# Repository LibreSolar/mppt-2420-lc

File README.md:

# MPPT Charger 20A

 Outdated design, development of new revision ongoing.

**Important:** As we are currently developing a new revision of this charge controller with several improvements, it is not recommended to rebuild this device anymore. Please see [this forum thread](https://talk.libre.solar/t/community-development-of-new-20a-mppt/121) and feel free to contribute your ideas.

## Features:
- 20A MPPT charger (buck converter)
- 55V max PV input
- 12V or 24V battery output
- 32bit ARM MCU (STM32F072)
- CAN communication interface with CANopen standard RJ45 jacks (including 10V power supply)
- Expandable via Olimex Universal Extension Connector (UEXT) featuring I2C, Serial and SPI interface (e.g. used for display, WIFI communication, etc.)
- Compatible to Hammond Mfg 1591XXCFL housing
- 5V switchable signal output
- USB connector for programming etc.
- Can be used as boost converter with software change
- Suitable for Li-Ion batteries with BMS (even recharge after low voltage disconnect possible, as the charge controller increases the voltage automatically when enoug sunlight is available)

## Built-in protection:
- Overvoltage
- Undervoltage
- Overcurrent
- PV short circuit
- PV reverse polarity (for max. module open circuit voltage of around 40V)
- Battery reverse polarity (destructive, fuse is blown)

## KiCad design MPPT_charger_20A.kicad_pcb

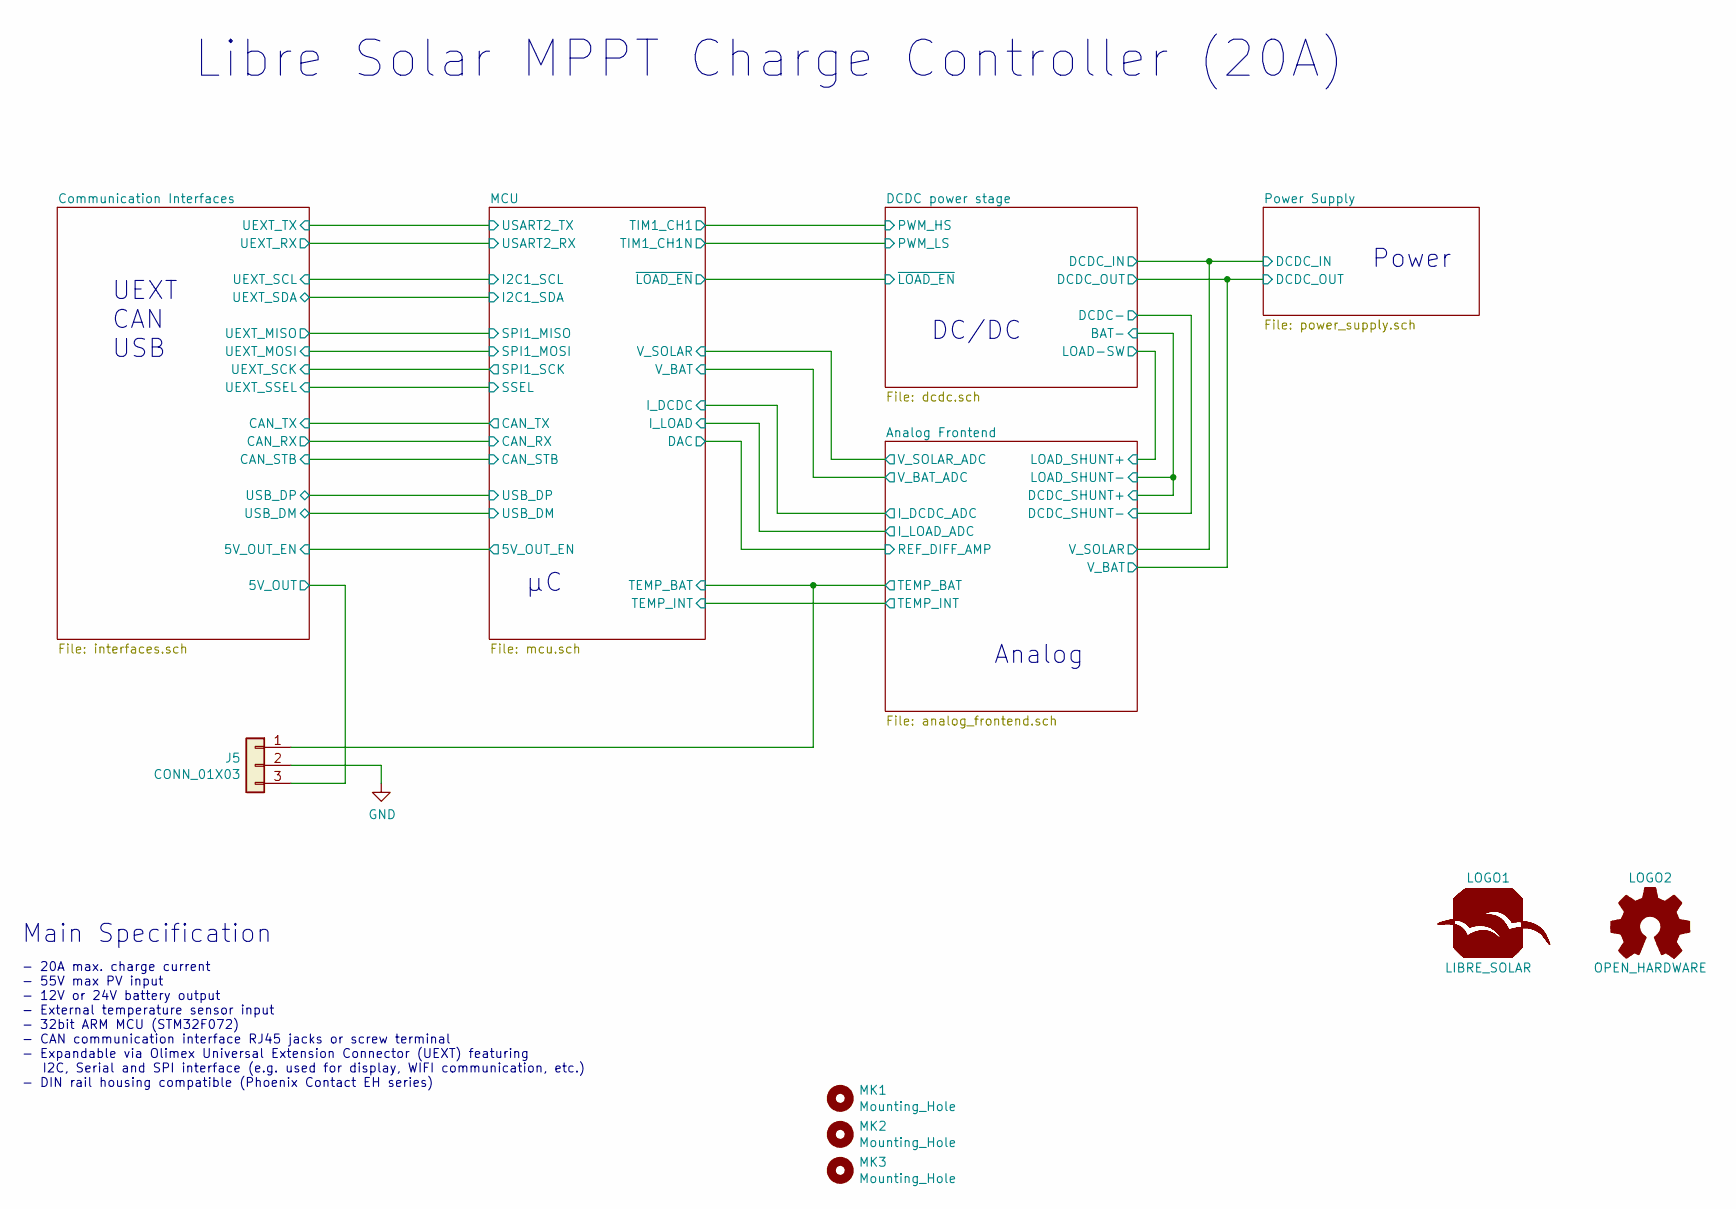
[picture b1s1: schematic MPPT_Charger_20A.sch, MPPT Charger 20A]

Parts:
J5: CONN_01X03; Phoenix_Contact_MC_1,5_3-G-3,81; PartNumber 1803280
LOGO1: LIBRE_SOLAR; LIBRESOLAR_LOGO
LOGO2: OPEN_HARDWARE; OSHW-Logo_5.7x6mm_SilkScreen
MK1, MK2, MK3: Mounting_Hole; MountingHole_3.2mm_M3

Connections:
/Analog Frontend/TEMP_BAT: J5.1; also elsewhere on the board
/Communication Interfaces/5V_OUT: J5.3; also elsewhere on the board
GND: J5.2; also elsewhere on the board

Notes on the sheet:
Libre Solar MPPT Charge Controller (20A)
Main Specification
- 20A max. charge current - 55V max PV input - 12V or 24V battery output - External temperature sensor input - 32bit ARM MCU (STM32F072) - CAN communication interface RJ45 jacks or screw terminal - Expandable via Olimex Universal Extension Connector (UEXT) featuring I2C, Serial and SPI interface (e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
UEXT CAN USB
DC/DC
Analog
Power

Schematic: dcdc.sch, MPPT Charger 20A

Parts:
C1, C2: 1000u; CP_Radial_D16.0mm_P7.50mm; PartNumber EKYB630ELL102ML25S
C3, C4: 4.7u; C_1210_3225; PartNumber GRJ32DC72A475KE11L
C5: 820u; CP_Radial_D10.0mm_P5.00mm; PartNumber EEU-FR1V821L
C6: 1n; C_0603_1608; PartNumber GRM1885C2A102JA01D
C7, C8, C27: 1u; C_0805_2012; PartNumber GRJ21BC72A105KE11L
C10: 100n; C_0603_1608; PartNumber GRM188R71H104KA93D
C12: 2.2u; C_0603_1608; PartNumber GRM188R61E225KA12D
C28: 10n; C_0603_1608; PartNumber GRM188R71H103KA01J
D1: 1N4148; D_SOD-123; PartNumber 1N4148W-7-F
D5: SMBJ36A; D_SMB; PartNumber SMBJ36A
F1: 25A; KEYSTONE-FUSE-3557-2; PartNumber 3557-2
J1: SOLAR; Phoenix_Contact_MKDS_5-2-952; PartNumber 1714971
J2: LOAD; Phoenix_Contact_MKDS_5-2-952; PartNumber 1714971
J3: BAT; Phoenix_Contact_MKDS_5-2-952; PartNumber 1714971
L1: 22uH; L-FERYSTER-DTMSS-27; PartNumber DTMSS-27/0,022/30-H
Q1, Q2, Q3, Q4: CSD18540Q5B; 5X6_MOSFET; PartNumber CSD18540Q5BT
R1, R3, R10: 3.3; R_0805_2012; PartNumber RC0805FR-073R3L
R2: 1M; R_0603_1608; PartNumber RC0603FR-071ML
R4: 2.2; R_1206_3216; PartNumber RC1206FR-072R2L
R6, R17: 2m; R_Bourns_CRE2512; PartNumber CRE2512-FZ-R002E-3
R9: 56k; R_0603_1608; PartNumber RC0603FR-0756KL
R12, R13: 2.2k; R_0603_1608; PartNumber RC0603FR-072K2L
R16: 10k; R_0603_1608; PartNumber RC0603FR-0710KL
T1: MMBT3904; SOT-23; PartNumber MMBT3904-7-F
U1: LM5107; SOIC-8_3.9x4.9mm_Pitch1.27mm; PartNumber LM5107MAX/NOPB

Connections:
+10V: C12.1, R9.2, U1.1 (VDD); also elsewhere on the board
/DCDC power stage/BAT+: C7.1, F1.2, J3.2
/DCDC power stage/BAT-: C7.2, J3.1, R6.2, R17.1; also elsewhere on the board
/DCDC power stage/DCDC_IN: C1.1, C2.1, C3.1, C4.1, C8.1, J1.2, Q1.D; also elsewhere on the board
/DCDC power stage/HS_DRV: R1.2, U1.7 (HO)
/DCDC power stage/LOAD-: C27.2, C28.2, D5.2 (A), J2.2, Q3.D
/DCDC power stage/LOAD-SW: Q3.S, R16.1, R17.2, T1.2 (E); also elsewhere on the board
/DCDC power stage/LS_DRV: R3.2, U1.5 (LO)
/DCDC power stage/PWM_HS: U1.2 (HI); also elsewhere on the board
/DCDC power stage/PWM_LS: U1.3 (LI); also elsewhere on the board
/DCDC power stage/SOLAR-: C8.2, J1.1, Q2.D
/DCDC power stage/SW_NODE: C10.2, L1.1, Q1.S, Q4.D, R4.2, U1.6 (HS)
/DCDC power stage/~LOAD_EN: R13.2; also elsewhere on the board
/DCDC_OUT: C5.1, C27.1, D5.1 (K), F1.1, J2.1, L1.2; also elsewhere on the board
GND: C1.2, C2.2, C3.2, C4.2, C5.2, C6.2, C12.2, Q2.S, Q4.S, R2.1, R6.1, U1.4 (VSS); also elsewhere on the board
unnamed: C6.1, R4.1
unnamed: C10.1, R10.1
unnamed: C28.1, Q3.G, R12.1
unnamed: D1.1, Q2.G, R2.2
unnamed: D1.2, Q4.G, R3.1
unnamed: Q1.G, R1.1
unnamed: R10.2, U1.8 (HB)
unnamed: R9.1, R12.2, T1.3 (C)
unnamed: R13.1, R16.2, T1.1 (B)

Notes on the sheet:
Solar Panel Voltage: 16-55 V
DC/DC power stage
Load output
MOSFET driver
Alternative: 330R at MOSFET gate --> 10.4/330 = 31 mA max
If not stated otherwise, all MLCC 50V X7R
MKDS_5/2-9,52
typisch: 1-10 nF + 10 uF

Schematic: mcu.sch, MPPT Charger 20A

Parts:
C22, C29, C30, C31, C32, C34: 100n; C_0603_1608; PartNumber GRM188R71H104KA93D
C33, C36: 2.2u; C_0603_1608; PartNumber GRM188R61E225KA12D
D6: LM4040CYM3-2.5; SOT-23; PartNumber LM4040DYM3-2.5-TR
L4: 600R; L_0603_1608Metric; PartNumber BLM18AG601SN1D
LED1: LED_red; LED_0603_1608Metric; PartNumber LTST-C190KRKT
LED2: LED_green; LED_0603_1608Metric; PartNumber LTST-C190GKT
P1: CONN_01X02; PinHeader_1x02_P2.54mm_Vertical
R31, R32, R41: 2.2k; R_0603_1608; PartNumber RC0603FR-072K2L
R37: 10k; R_0603_1608; PartNumber RC0603FR-0710KL
R39, R40: 1M; R_0603_1608; PartNumber RC0603FR-071ML
R42, R43: 330; R_0603_1608; PartNumber RC0603FR-07330RL
R45: 56k; R_0603_1608; PartNumber RC0603FR-0756KL
SW1: SW_PUSH; SW_SPST_EVQP7A; PartNumber PTS840 GK SMTR LFS
SWD1: ST_Nucleo_SWD; PinHeader_1x06_P2.54mm_Vertical
T2: MMBT3904; SOT-23; PartNumber MMBT3904-7-F
U2: STM32F072CB; LQFP-48_7x7mm_P0.5mm; PartNumber STM32F072CBT6
U6: 24AA01; SOT-23-5; PartNumber 24AA32AFT-I/OT
Y1: 8MHz; Resonator_Murata_CSTCE_G; PartNumber CSTCE8M00G15C99-R0

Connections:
+3V3: C22.1, C30.1, C31.1, C32.1, C33.1, L4.1, R31.2, R32.2, R37.2, R39.2, R40.2, SWD1.1 (VCC), U2.1 (VBAT), U2.24 (VDD_1), U2.36 (VDD_2), U2.48 (VDD_3), U6.4 (VCC); also elsewhere on the board
/Analog Frontend/TEMP_BAT: U2.10 (PA0-WKUP); also elsewhere on the board
/Analog Frontend/TEMP_INT: U2.11 (PA1); also elsewhere on the board
/Communication Interfaces/5V_OUT_EN: U2.25 (PB12); also elsewhere on the board
/Communication Interfaces/CAN_RX: U2.45 (PB8); also elsewhere on the board
/Communication Interfaces/CAN_STB: U2.38 (PA15); also elsewhere on the board
/Communication Interfaces/CAN_TX: U2.46 (PB9); also elsewhere on the board
/Communication Interfaces/UEXT_EN: U2.3 (PC14-OSC32_IN); also elsewhere on the board
/Communication Interfaces/UEXT_RX: U2.13 (PA3); also elsewhere on the board
/Communication Interfaces/UEXT_TX: U2.12 (PA2); also elsewhere on the board
/Communication Interfaces/USB_DM: U2.32 (PA11); also elsewhere on the board
/Communication Interfaces/USB_DP: U2.33 (PA12); also elsewhere on the board
/Communication Interfaces/V_BUS_EN: U2.4 (PC15-OSC32_OUT); also elsewhere on the board
/DCDC power stage/PWM_HS: U2.29 (PA8); also elsewhere on the board
/DCDC power stage/PWM_LS: U2.26 (PB13); also elsewhere on the board
/DCDC power stage/~LOAD_EN: U2.20 (PB2); also elsewhere on the board
/MCU/BOOT0: C36.1, R39.1, R41.2, U2.44 (BOOT0)
/MCU/DAC: U2.14 (PA4); also elsewhere on the board
/MCU/I2C1_SCL: U2.42 (PB6); also elsewhere on the board
/MCU/I2C1_SDA: U2.43 (PB7); also elsewhere on the board
/MCU/I2C2_SCL: R31.1, U2.21 (PB10), U6.1 (SCL)
/MCU/I2C2_SDA: R32.1, U2.22 (PB11), U6.3 (SDA)
/MCU/I_DCDC: U2.19 (PB1); also elsewhere on the board
/MCU/I_LOAD: U2.18 (PB0); also elsewhere on the board
/MCU/LED1: R42.2, U2.27 (PB14)
/MCU/LED2: R43.2, U2.28 (PB15)
/MCU/OSC_IN: U2.5 (PD0-OSC_IN), Y1.1
/MCU/OSC_OUT: U2.6 (PD1-OSC_OUT), Y1.3
/MCU/SPI1_MISO: U2.40 (PB4); also elsewhere on the board
/MCU/SPI1_MOSI: U2.41 (PB5); also elsewhere on the board
/MCU/SPI1_SCK: U2.39 (PB3); also elsewhere on the board
/MCU/SSEL: U2.2 (PC13-TAMPER-RTC); also elsewhere on the board
/MCU/SWCLK: SWD1.2 (SWCLK), U2.37 (PA14)
/MCU/SWDIO: SWD1.4 (SWDIO), U2.34 (PA13)
/MCU/USART1_RX: P1.2, U2.31 (PA10)
/MCU/USART1_TX: P1.1, U2.30 (PA9)
/MCU/V_BAT: U2.16 (PA6); also elsewhere on the board
/MCU/V_REF: D6.1 (K), R37.1, U2.15 (PA5)
/MCU/V_SOLAR: U2.17 (PA7); also elsewhere on the board
/MCU/~RESET: C29.1, R40.1, R45.1, SW1.1, SWD1.5 (NRST), U2.7 (NRST)
GND: C22.2, C29.2, C30.2, C31.2, C32.2, C33.2, C34.2, C36.2, D6.2 (A), LED1.1, LED2.1, SW1.2, SWD1.3 (GND), T2.2 (E), U2.8 (VSSA), U2.23 (VSS_1), U2.35 (VSS_2), U2.47 (VSS_3), U6.2 (GND), U6.5 (WP), Y1.2; also elsewhere on the board
unnamed: C34.1, L4.2, U2.9 (VDDA)
unnamed: LED1.2, R42.1
unnamed: LED2.2, R43.1
unnamed: R41.1, T2.3 (C)
unnamed: R45.2, T2.1 (B)

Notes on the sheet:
Status LEDs
MCU STM32F072
STM Nucleo SWD and USART
min. 65 uA operating current
Voltage reference
Reset and boot circuit
Tight tolerance for CAN interface
Equations: tau = R39 * C36 = 2.2 s V(t) = Vmax * (1-exp(-t/tau)) --> t = -tau * ln(1-V/Vmax) Normal startup: BOOT0 < 0.69 V Press SW1 < 0.51 s USB bootloader: BOOT0 > 1.61 V Press SW1 > 1.47 s
EEPROM
If not stated otherwise, all MLCC 50V X7R

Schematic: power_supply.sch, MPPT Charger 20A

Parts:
C14: 1u; C_0805_2012; PartNumber GRJ21BC72A105KE11L
C15: 4.7u; C_1210_3225; PartNumber GRJ32DC72A475KE11L
C19: 100n; C_0603_1608; PartNumber GRM188R71H104KA93D
C20, C21, C24: 10u; C_0805_2012; PartNumber GRM21BR61E106KA73L
C23, C38: 2.2u; C_0603_1608; PartNumber GRM188R61E225KA12D
C35: 100p; C_0603_1608; PartNumber GRM1885C2A101JA01D
D2: SS16FP; D_PowerDI-123; PartNumber SS16FP
L2: 4.7uH; L_0805_2012Metric; PartNumber LQM21PN4R7NGRD
L3: 47uH; Bourns_SRN6045TA; PartNumber NR6045T470M
R28: 110k; R_0603_1608; PartNumber RC0603FR-07110KL
R29: 10k; R_0603_1608; PartNumber RC0603FR-0710KL
R50: 1M; R_0603_1608; PartNumber RC0603FR-071ML
U3: AZ1117; SOT-223-3_TabPin2; PartNumber AZ1117EH-5.0TRG1
U4: MP2459; SOT-23-6; PartNumber MP2459GJ-Z
U5: AP2210-3.3; SOT-23-5; PartNumber AP2210K-3.3TRG1

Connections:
+3V3: C38.1, U5.5 (OUT); also elsewhere on the board
+5V: C23.1, C24.1, U3.2 (OUT), U5.1 (IN), U5.3 (EN); also elsewhere on the board
+10V: C20.1, C21.1, L3.2, R28.1, U3.3 (IN); also elsewhere on the board
/DCDC power stage/DCDC_IN: C14.1, L2.1; also elsewhere on the board
GND: C14.2, C15.2, C20.2, C21.2, C23.2, C24.2, C35.2, C38.2, D2.2, R29.2, U3.1 (GND), U4.2 (GND), U5.2 (GND); also elsewhere on the board
unnamed: C15.1, L2.2, R50.2, U4.5 (Vin)
unnamed: C19.1, U4.1 (CB)
unnamed: C19.2, D2.1, L3.1, U4.6 (SW)
unnamed: C35.1, U5.4 (BP)
unnamed: R28.2, R29.1, U4.3 (FB)
unnamed: R50.1, U4.4 (EN)

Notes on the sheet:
Max current output: 150mA
Solar/Battery to 10V (SMPS)
5V to 3.3V (LDO)
Place close to SMPS
10V to 5V (LDO)
Advantages of DCDC_IN as input: - Power supply possible through solar or battery (via HS MOSFET body diode) - Discharged Li-ion batteries (with enabled cut-off switch) can be recharged
If not stated otherwise, all MLCC 50V X7R
MP2459: R50 necessary to limit current into EN to <100uA R28 selection: 110k for MP2459 (9.7 V) 120k for LMR16006X (10 V)

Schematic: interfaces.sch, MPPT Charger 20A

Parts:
C25, C26, C39: 100n; C_0603_1608; PartNumber GRM188R71H104KA93D
D3: USBLC6-2SC6Y; SOT-23-6; PartNumber USBLC6-2SC6Y
D4: NUP2105L; SOT-23; PartNumber NUP2105LT1G
D8: MM3Z12VT1G; D_SOD-323; PartNumber MM3Z12VT1G
D9, D10: 1N4148; D_SOD-123; PartNumber 1N4148W-7-F
F2, F3: 200mA; R_1206_3216; PartNumber 0ZCJ0020FF2E
J4: UEXT; Box_Header_2x05x2.54mm_Straight
JP1, JP2: RJ45_NS; RJ45_8P8C; PartNumber 54602-908LF
JP3: Jumper_NC_Small; PinHeader_1x02_P2.54mm_Horizontal
P3: USB Micro B; USB_Micro-B_10103594-0001LF; PartNumber 10103594-0001LF
Q5, Q6, Q7: BSS84; SOT-23; PartNumber BSS84
R5, R33, R46, R47: 100k; R_0603_1608; PartNumber RC0603FR-07100KL
R30, R49: 56k; R_0603_1608; PartNumber RC0603FR-0756KL
R34, R35, R38: 2.2k; R_0603_1608; PartNumber RC0603FR-072K2L
R36: 120; R_1206_3216; PartNumber RC1206FR-07120RL
R48: 10k; R_0603_1608; PartNumber RC0603FR-0710KL
T3, T4: MMBT3904; SOT-23; PartNumber MMBT3904-7-F
U8: TJA1042T/3; SOIC-8_3.9x4.9mm_Pitch1.27mm; PartNumber TJA1042T/3/1J

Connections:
+3V3: C39.1, Q6.2 (S), R5.1, R34.2, R35.2, U8.5 (VIO); also elsewhere on the board
+5V: C26.1, F2.1, Q5.2 (S), R33.1, U8.3 (VCC); also elsewhere on the board
/Communication Interfaces/5V_OUT: Q5.3 (D); also elsewhere on the board
/Communication Interfaces/5V_OUT_EN: R47.2; also elsewhere on the board
/Communication Interfaces/CAN_GND: D10.2, JP1.3, JP1.7, JP2.3, JP2.7
/Communication Interfaces/CAN_H: D4.1, JP1.1, JP2.1, JP3.1, U8.7 (CANH)
/Communication Interfaces/CAN_L: D4.2, JP1.2, JP2.2, R36.2, U8.6 (CANL)
/Communication Interfaces/CAN_RX: U8.4 (RXD); also elsewhere on the board
/Communication Interfaces/CAN_SHLD: JP1.6, JP2.6
/Communication Interfaces/CAN_STB: U8.8 (STB); also elsewhere on the board
/Communication Interfaces/CAN_TX: U8.1 (TXD); also elsewhere on the board
/Communication Interfaces/CAN_V+: D9.1, JP1.8, JP2.8
/Communication Interfaces/RJ45_4: JP1.4, JP2.4
/Communication Interfaces/RJ45_5: JP1.5, JP2.5
/Communication Interfaces/UEXT_EN: Q6.1 (G), R5.2; also elsewhere on the board
/Communication Interfaces/UEXT_RX: J4.4 (RXD); also elsewhere on the board
/Communication Interfaces/UEXT_TX: J4.3 (TXD); also elsewhere on the board
/Communication Interfaces/USB_DM: D3.3 (IO2); also elsewhere on the board
/Communication Interfaces/USB_DP: D3.1 (IO1); also elsewhere on the board
/Communication Interfaces/V_BUS_EN: R48.2; also elsewhere on the board
/DCDC_OUT: D8.1 (K), Q7.2 (S), R49.1; also elsewhere on the board
/MCU/I2C1_SCL: J4.5 (SCL), R35.1; also elsewhere on the board
/MCU/I2C1_SDA: J4.6 (SDA), R34.1; also elsewhere on the board
/MCU/SPI1_MISO: J4.7 (MISO); also elsewhere on the board
/MCU/SPI1_MOSI: J4.8 (MOSI); also elsewhere on the board
/MCU/SPI1_SCK: J4.9 (SCK); also elsewhere on the board
/MCU/SSEL: J4.10 (SSEL); also elsewhere on the board
GND: C25.2, C26.2, C39.2, D3.2 (GND), D4.3, D10.1, J4.2 (GND), P3.5 (GND), R46.2, T3.2 (E), T4.2 (E), U8.2 (GND); also elsewhere on the board
unnamed: C25.1, P3.6 (Shield)
unnamed: D3.4 (IO2), P3.2 (D-)
unnamed: D3.5 (VBUS), F2.2, P3.1 (VBUS)
unnamed: D3.6 (IO1), P3.3 (D+)
unnamed: D8.2 (A), Q7.1 (G), R30.1, R49.2
unnamed: D9.2, F3.1
unnamed: F3.2, Q7.3 (D)
unnamed: J4.1 (3V3), Q6.3 (D)
unnamed: JP3.2, R36.1
unnamed: P3.4 (ID), R46.1
unnamed: Q5.1 (G), R33.2, R38.1
unnamed: R30.2, T3.3 (C)
unnamed: R38.2, T4.3 (C)
unnamed: R47.1, T4.1 (B)
unnamed: R48.1, T3.1 (B)

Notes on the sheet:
CAN interface
Extension connector
I2C pull-ups
USB connector
5V signal output
ToDo: check R47 --> should be smaller?
Bus power supply
If not stated otherwise, all MLCC 50V X7R

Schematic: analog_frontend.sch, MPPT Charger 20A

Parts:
C9, C16, C40, C42: 100n; C_0603_1608; PartNumber GRM188R71H104KA93D
C11, C13, C17, C18: 10n; C_0603_1608; PartNumber GRM188R71H103KA01J
R7, R8, R11, R18, R19, R20: 2.2k; R_0603_1608; PartNumber RC0603FR-072K2L
R14, R15, R21, R22: 150k; R_0603_1608; PartNumber RC0603FR-07150KL
R23, R27, R44: 10k; R_0603_1608; PartNumber RC0603FR-0710KL
R24, R25: 100k; R_0603_1608; PartNumber RC0603FR-07100KL
R26: 5.6k; R_0603_1608; PartNumber RC0603FR-075K6L
RT1: 10k; R_0603_1608; PartNumber NTCG163JF103FT1S
U7: LM258; SOIC-8_3.9x4.9mm_Pitch1.27mm; PartNumber LM258DR

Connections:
+3V3: R23.1, R44.1; also elsewhere on the board
+5V: C9.1, U7.8 (V+); also elsewhere on the board
/Analog Frontend/TEMP_BAT: C40.1, R44.2; also elsewhere on the board
/Analog Frontend/TEMP_INT: C16.1, R23.2, RT1.1; also elsewhere on the board
/DCDC power stage/BAT-: R7.2, R19.2; also elsewhere on the board
/DCDC power stage/DCDC_IN: R24.1; also elsewhere on the board
/DCDC power stage/LOAD-SW: R8.2; also elsewhere on the board
/DCDC_OUT: R25.1; also elsewhere on the board
/MCU/DAC: C42.1, R14.1, R21.2; also elsewhere on the board
/MCU/I_DCDC: C13.1, R20.2; also elsewhere on the board
/MCU/I_LOAD: C11.1, R11.2; also elsewhere on the board
/MCU/V_BAT: C18.1, R25.2, R27.1; also elsewhere on the board
/MCU/V_SOLAR: C17.1, R24.2, R26.1; also elsewhere on the board
GND: C9.2, C11.2, C13.2, C16.2, C17.2, C18.2, C40.2, C42.2, R18.2, R26.2, R27.2, RT1.2, U7.4 (V-); also elsewhere on the board
unnamed: R11.1, R15.2, U7.7
unnamed: R8.1, R14.2, U7.5 (+)
unnamed: R7.1, R15.1, U7.6 (-)
unnamed: R18.1, R22.1, U7.2 (-)
unnamed: R19.1, R21.1, U7.3 (+)
unnamed: R20.1, R22.2, U7.1

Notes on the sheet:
Load current
DCDC current
Solar and battery voltage
Diff. amp. reference defined by DAC pin instead of GND: variable zero current set point
If not stated otherwise, all MLCC 50V X7R
Temperature (ext./int.)

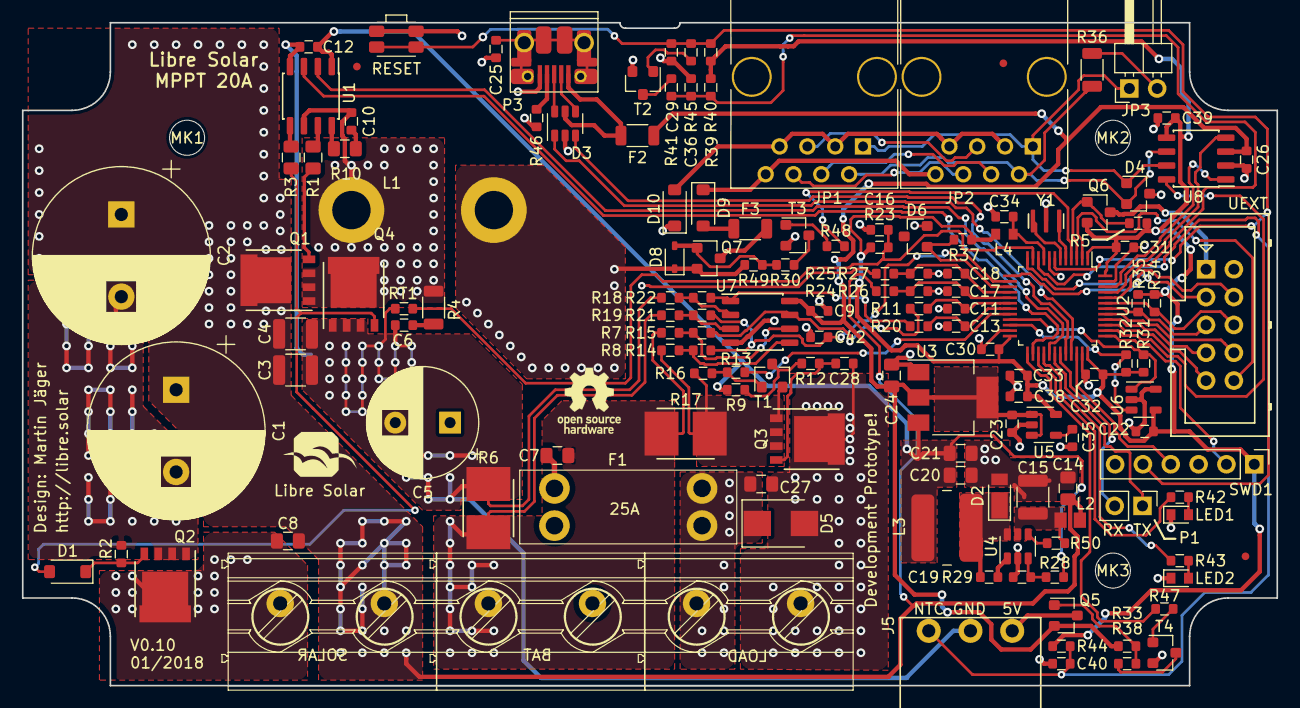
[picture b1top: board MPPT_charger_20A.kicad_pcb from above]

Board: 2 copper layers, 114.5 x 60.5 mm, 146 parts (0 on the bottom side), 102 nets.

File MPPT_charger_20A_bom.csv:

Component;Description;Part;References;Value;Footprint;Quantity Per PCB;Datasheet;Remarks;PartNumber;Manufacturer;Alternative;Supplier
1;Polarised capacitor;CP_Small;C1 C2;1000u;CP_Radial_D16.0mm_P7.50mm;2;;63V, 2.74A, 16x25;EKYB630ELL102ML25S;United Chemi-Con;;
2;Unpolarized capacitor;C_Small;C9 C10 C16 C19 C22 C25 C26 C29 C30 C31 C32 C34 C39 C40 C42;100n;C_0603_1608;15;;;GRM188R71H104KA93D;Murata;;
3;Unpolarized capacitor;C_Small;C35;100p;C_0603_1608;1;;;GRM1885C2A101JA01D;Murata;;
4;Unpolarized capacitor;C_Small;C11 C13 C17 C18 C28;10n;C_0603_1608;5;;;GRM188R71H103KA01J;Murata;;
5;Unpolarized capacitor;C_Small;C20 C21 C24;10u;C_0805_2012;3;;25V;GRM21BR61E106KA73L;Murata;;
6;Unpolarized capacitor;C_Small;C6;1n;C_0603_1608;1;;NP0/C0G;GRM1885C2A102JA01D;Murata;;
7;Unpolarized capacitor;C_Small;C7 C8 C14 C27;1u;C_0805_2012;4;;100V, X7S;GRJ21BC72A105KE11L;Murata;;
8;Unpolarized capacitor;C_Small;C12 C23 C33 C36 C38;2.2u;C_0603_1608;5;;25V, X5R;GRM188R61E225KA12D;Murata;;
9;Unpolarized capacitor;C_Small;C3 C4 C15;4.7u;C_1210_3225;3;;100V, X7S;GRJ32DC72A475KE11L;Murata;;
10;Polarised capacitor;CP_Small;C5;820u;CP_Radial_D10.0mm_P5.00mm;1;;35V, 2.47A;EEU-FR1V821L;Panasonic;;
11;Diode, small symbol;D_Small;D1 D9 D10;1N4148;D_SOD-123;3;;;1N4148W-7-F;Diodes Inc.;;
12;Zener Diode, small symbol;D_Zener_Small;D6;LM4040CYM3-2.5;SOT-23;1;https://en.wikipedia.org/wiki/Zener_diode;;LM4040DYM3-2.5-TR;Microchip;;
13;Zener Diode, small symbol;D_Zener_Small;D8;MM3Z12VT1G;D_SOD-323;1;https://en.wikipedia.org/wiki/Zener_diode;;MM3Z12VT1G;ON Semiconductor;;
14;;NUP2105L;D4;NUP2105L;SOT-23;1;;;NUP2105LT1G;ON Semiconductor;SZNUP2105L;
15;Zener Diode, small symbol;D_Zener_Small;D5;SMBJ36A;D_SMB;1;https://en.wikipedia.org/wiki/Zener_diode;;SMBJ36A;Bourns;;
16;Schottky diode, small symbol;D_Schottky_Small;D2;SS16FP;D_PowerDI-123;1;;;SS16FP;Diodes Inc.;DFLS160-7;
17;;USBLC6-2SC6;D3;USBLC6-2SC6Y;SOT-23-6;1;;;USBLC6-2SC6Y;STMicroelectronics;;
18;resettable fuse, polymeric positive temperature coefficient (PPTC);Polyfuse;F2 F3;200mA;R_1206_3216;2;;;0ZCJ0020FF2E;Bel;;
19;Fuse, small symbol;Fuse_Small;F1;25A;KEYSTONE-FUSE-3557-2;1;;;3557-2;Keystone;;
20;;Screw_Terminal_1x02;J3;BAT;Phoenix_Contact_MKDS_5-2-952;1;;;1714971;Phoenix Contact;;
21;Generic connector, single row, 01x03;Conn_01x03;J5;CONN_01X03;Phoenix_Contact_MC_1,5_3-G-3,81;1;;;1803280;Phoenix Contact;;
22;;Screw_Terminal_1x02;J2;LOAD;Phoenix_Contact_MKDS_5-2-952;1;;;1714971;Phoenix Contact;;
23;;Screw_Terminal_1x02;J1;SOLAR;Phoenix_Contact_MKDS_5-2-952;1;;;1714971;Phoenix Contact;;
24;;UEXT;J4;UEXT;Box_Header_2x05x2.54mm_Straight;1;;;;;;
25;Jumper, normally closed;Jumper_NC_Small;JP3;Jumper_NC_Small;Pin_Header_Angled_1x02_Pitch2.54mm;1;;;;;;
26;;RJ45_NS;JP1 JP2;RJ45_NS;RJ45_8P8C;2;;;54602-908LF;Amphenol FCI;;
27;Inductor with Iron Core;L_Core_Iron;L1;22uH;L-FERYSTER-DTMSS-27;1;;;DTMSS-27/0,022/30-H;Feryster;;Feryster
28;Inductor, small symbol;L_Small;L2;4.7uH;L_0805;1;;;LQM21PN4R7NGRD;Murata;;
29;Inductor, small symbol;L_Small;L3;47uH;Bourns_SRN6045TA;1;;;NR6045T470M;Tayo Yuden;Bourns SRR6045TA-470Y;
30;Inductor, small symbol;L_Small;L4;600R;L_0603;1;;;BLM18AG601SN1D;Murata;;
31;LED, small symbol;LED_Small;LED2;LED_green;LED_0603;1;;;LTST-C190GKT;Lite-On;;
32;LED, small symbol;LED_Small;LED1;LED_red;LED_0603;1;;red;LTST-C190KRKT;Lite-On;;
33;Generic connector, single row, 01x02;Conn_01x02;P1;CONN_01X02;Pin_Header_Straight_1x02_Pitch2.54mm;1;;;;;;
34;USB Micro Type B connector;USB_B_Micro;P3;USB Micro B;USB_Micro-B_10103594-0001LF;1;;;10103594-0001LF;FCI;;Mouser
35;Transistor P-MOSFET with substrate diode (general);Q_PMOS_GSD;Q5 Q6 Q7;BSS84;SOT-23;3;;;BSS84;Fairchild;;
36;Transistor N-MOSFET (general);Q_NMOS;Q1 Q2 Q3 Q4;CSD18540Q5B;5X6_MOSFET;4;;;CSD18540Q5BT;Texas Instruments;;
37;Resistor, small symbol;R_Small;R5 R24 R25 R33 R46 R47;100k;R_0603_1608;6;;;RC0603FR-07100KL;Yageo;;
38;Resistor, small symbol;R_Small;R16 R23 R27 R29 R37 R44 R48;10k;R_0603_1608;7;;;RC0603FR-0710KL;Yageo;;
39;Resistor, small symbol;R_Small;R28;110k;R_0603_1608;1;;;RC0603FR-07110KL;Yageo;;
40;Resistor, small symbol;R_Small;R36;120;R_1206_3216;1;;;RC1206FR-07120RL;Yageo;;
41;Resistor, small symbol;R_Small;R14 R15 R21 R22;150k;R_0603_1608;4;;;RC0603FR-07150KL;Yageo;;
42;Resistor, small symbol;R_Small;R2 R39 R40 R50;1M;R_0603_1608;4;;;RC0603FR-071ML;Yageo;;
43;Resistor, small symbol;R_Small;R4;2.2;R_1206_3216;1;;;RC1206FR-072R2L;Yageo;;
44;Resistor, small symbol;R_Small;R7 R8 R11 R12 R13 R18 R19 R20 R31 R32 R34 R35 R38 R41;2.2k;R_0603_1608;14;;;RC0603FR-072K2L;Yageo;;
45;Resistor, small symbol;R_Small;R6 R17;2m;R_Bourns_CRE2512;2;;;CRE2512-FZ-R002E-3;Bourns;;
46;Resistor, small symbol;R_Small;R1 R3 R10;3.3;R_0805_2012;3;;;RC0805FR-073R3L;Yageo;;
47;Resistor, small symbol;R_Small;R42 R43;330;R_0603_1608;2;;;RC0603FR-07330RL;Yageo;;
48;Resistor, small symbol;R_Small;R26;5.6k;R_0603_1608;1;;;RC0603FR-075K6L;Yageo;;
49;Resistor, small symbol;R_Small;R9 R30 R45 R49;56k;R_0603_1608;4;;;RC0603FR-0756KL;Yageo;;
50;;Thermistor_NTC;RT1;10k;R_0603_1608;1;;;NTCG163JF103FT1S;TDK;;
51;Button;SW_PUSH;SW1;SW_PUSH;SW_SPST_EVQP7A;1;;;PTS840 GK SMTR LFS;C&K Components;;
52;;ST_Nucleo_SWD;SWD1;ST_Nucleo_SWD;Pin_Header_Straight_1x06_Pitch2.54mm;1;;;;;;
53;45V Vce, 0.8A Ic, NPN, SOT-23;BC817;T1 T2 T3 T4;MMBT3904;SOT-23;4;http://www.fairchildsemi.com/ds/BC/BC817.pdf;;MMBT3904-7-F;Diodes Inc.;;
54;Microchip 24AA01 1K I2C EEPROM;24AA01;U6;24AA01;SOT-23-5;1;;;24AA32AFT-I/OT;Microchip;;
55;300mA low dropout linear regulator, shutdown pin, 1.5V fixed positive output, SOT-23-5 package;AP2210-3.3;U5;AP2210-3.3;SOT-23-5;1;http://www.diodes.com/_files/datasheets/AP131.pdf;;AP2210K-3.3TRG1;Diodes Inc.;MIC5225;
56;;AZ1117;U3;AZ1117;SOT-223-3Lead_TabPin2;1;;;AZ1117EH-5.0TRG1;Diodes Inc.;;
57;Dual Opamp, SOIC-8/DIP-8/SSOP-8/TO-99;Opamp_Dual_Generic;U7;LM258;SOIC-8_3.9x4.9mm_Pitch1.27mm;1;;;LM258DR;Texas Instruments;;
58;;LM5107;U1;LM5107;SOIC-8_3.9x4.9mm_Pitch1.27mm;1;;;LM5107MAX/NOPB;Texas Instruments;;
59;SIMPLE SWITCHER® 4V to 60V, 600mA Step-Down Regulator with Low Iq;LMR16006;U4;MP2459;SOT-23-6;1;;;MP2459GJ-Z;Monolithic Power;LMR16006XDDCR;
60;;STM32F072CB;U2;STM32F072CB;LQFP-48_7x7mm_Pitch0.5mm;1;;;STM32F072CBT6;STMicroelectronics;;
61;TJA1042T/3, High-Speed CAN Transceiver, separate VIO, standby mode, SOIC-8;TJA1042T-3;U8;TJA1042T/3;SOIC-8_3.9x4.9mm_Pitch1.27mm;1;http://www.nxp.com/documents/data_sheet/TJA1042.pdf;;TJA1042T/3/1J;NXP;;Mouser
62;Three pin ceramic resonator;Resonator_Small;Y1;8MHz;Resonator_Murata_CSTCE_G;1;;0.1% tolerance;CSTCE8M00G15C99-R0;Murata;;





Component Groups:;62
Component Count:;141
Fitted Components:;141
Number of PCBs:;1
Total components:;141
Schematic Version:;0.10
Schematic Date:;2018-01-18
BoM Date:;26/01/2018 20:05:44
Schematic Source:;D:\LibreSolar\2_Development\04_Hardware\MPPT-Charger_20A\MPPT_charger_20A.sch
KiCad Version:;Eeschema (2017-11-18 revision ff5ee05de)-makepkg

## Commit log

2016-06-05 Initial commit of schematic and board
2016-06-05 PDF/PNG of schematic/board files uploaded
2016-06-05 Update of PDF
2016-06-05 Fixed clearance at some vias (DRC error)
2016-07-28 Foto of board uploaded
2016-12-13 Updated revision with 20A charge current
2016-12-17 Minor changes + nice image from Aisler.net
2017-01-17 Fixing issues #12 and #11
2017-03-22 Rev 0.7: moved to KiCAD
2017-03-22 Removed temporary files from repository.
2017-03-25 Library added as sub-module
2017-03-26 Updated R/C/L symbols to IEC 60617 style
2017-08-06 Updated revision: 0.8
2017-08-15 Minor changes and gerber export update
2017-11-29 rename files (append _lowercase)
2017-11-29 V0.8.1: Small changes and update to new kicad symbol library table (nightlies only)
2017-11-29 change of schematic to lowercase (_lowercase appended)
2017-11-29 Change of schematic file name to lowercase
2017-12-03 Bus power supply from battery instead of 10V rail
2017-12-11 Revision 0.9 for first small production batch - Switchable power supply for bus and UEXT (to be make sure to reach very low power consumption during LVD conditions) - MLCCs for EMC added to each high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
2017-12-11 BOM updated
2018-01-18 Final version for Jan/2018 production
2018-01-26 Adjustments to use MP2459 as SMPS (previous one out of stock)
2018-01-26 Power supply inductor changed to Tayo Yuden
2018-05-12 Update to KiCad 5 schematic library
2018-05-12 BOM update
2019-03-05 Create LM5107.pdf
    Adding main components datasheets
2019-10-05 Note regarding development of new version added
